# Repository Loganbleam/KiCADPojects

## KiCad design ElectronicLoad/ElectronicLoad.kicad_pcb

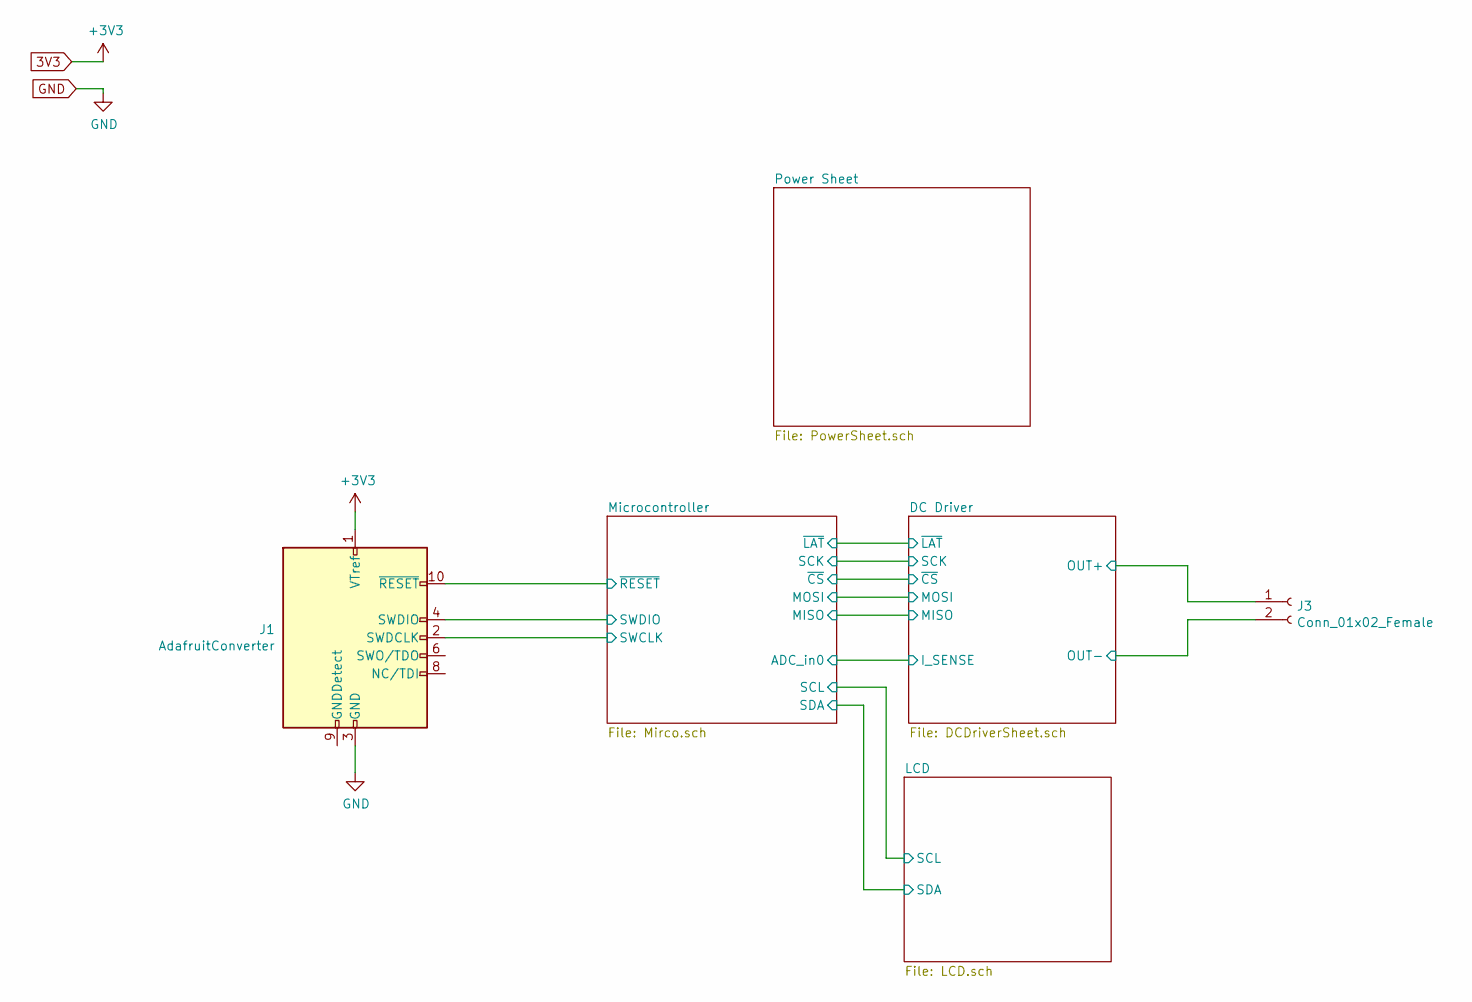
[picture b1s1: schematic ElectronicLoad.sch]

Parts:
J1: AdafruitConverter; PinHeader_2x05_P1.27mm_Vertical_SMD
J3: Conn_01x02_Female; 5.7pitchHoles

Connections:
3V3: J1.1 (VTref); also elsewhere on the board
/Microcontroller/SWCLK: J1.2 (SWDCLK); also elsewhere on the board
/Microcontroller/SWDIO: J1.4 (SWDIO); also elsewhere on the board
/Microcontroller/~RESET: J1.10 (~RESET~); also elsewhere on the board
GND: J1.3 (GND), J1.5 (GND), J1.9 (GNDDetect), J3.2; also elsewhere on the board

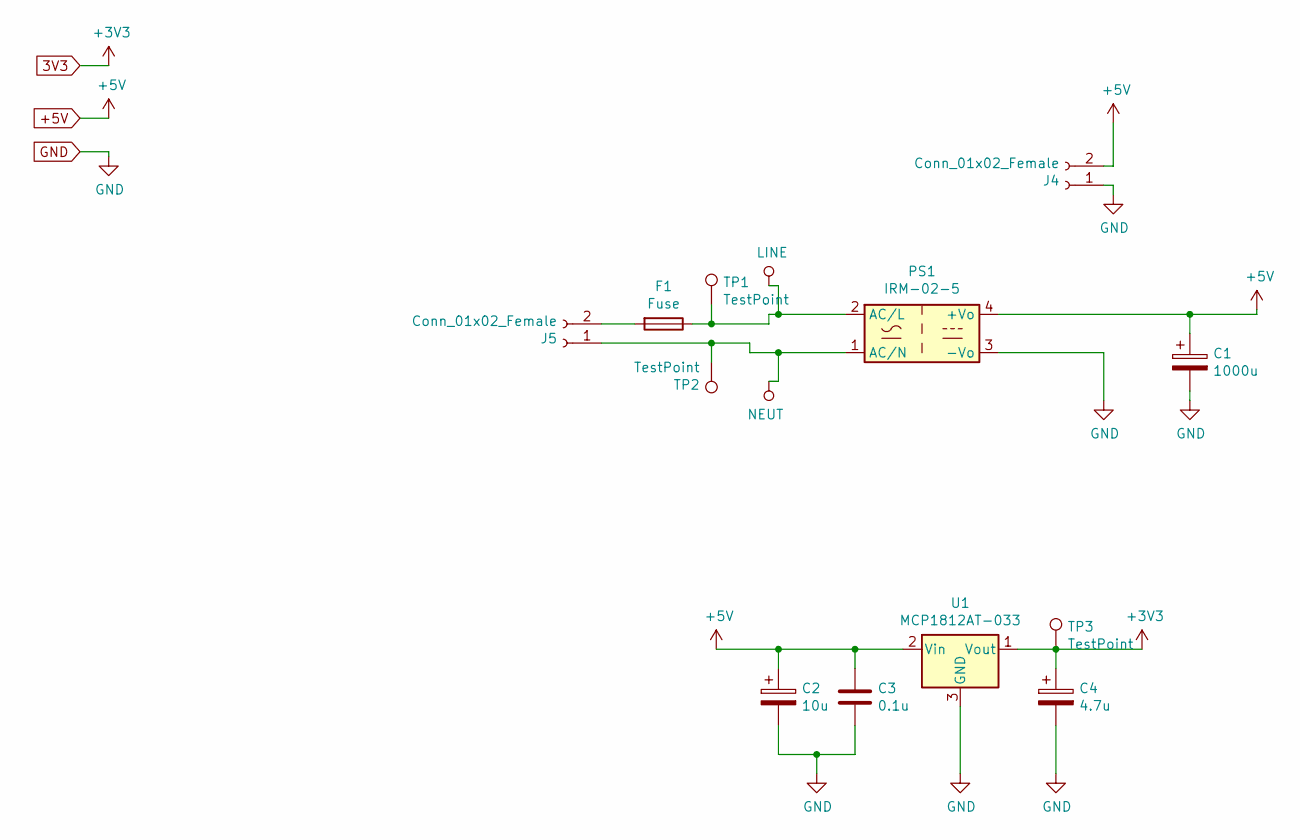
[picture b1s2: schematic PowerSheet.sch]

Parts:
C1: 1000u; CP_Elec_16x17.5
C2: 10u; CP_Elec_6.3x7.7
C3: 0.1u; C_0603_1608Metric
C4: 4.7u; CP_Elec_4x4.5
F1: Fuse; FuseHolder5x20
J4: Conn_01x02_Female; PinSocket_1x02_P2.54mm_Vertical
J5: Conn_01x02_Female; 16GAWire1x02
PS1: IRM-02-5; Converter_ACDC_MeanWell_IRM-02-xx_THT
TP1, TP2, TP3: TestPoint; TestPoint_THTPad_D1.5mm_Drill0.7mm
U1: MCP1812AT-033; SOT-23

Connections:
3V3: C4.1, TP3.1, U1.1 (Vout); also elsewhere on the board
+5V: C1.1, C2.1, C3.1, J4.2, PS1.4 (+Vo), U1.2 (Vin); also elsewhere on the board
GND: C1.2, C2.2, C3.2, C4.2, J4.1, PS1.3 (-Vo), U1.3 (GND); also elsewhere on the board
LINE: F1.1, PS1.2 (AC/L), TP1.1
NEUT: J5.1, PS1.1 (AC/N), TP2.1
unnamed: F1.2, J5.2

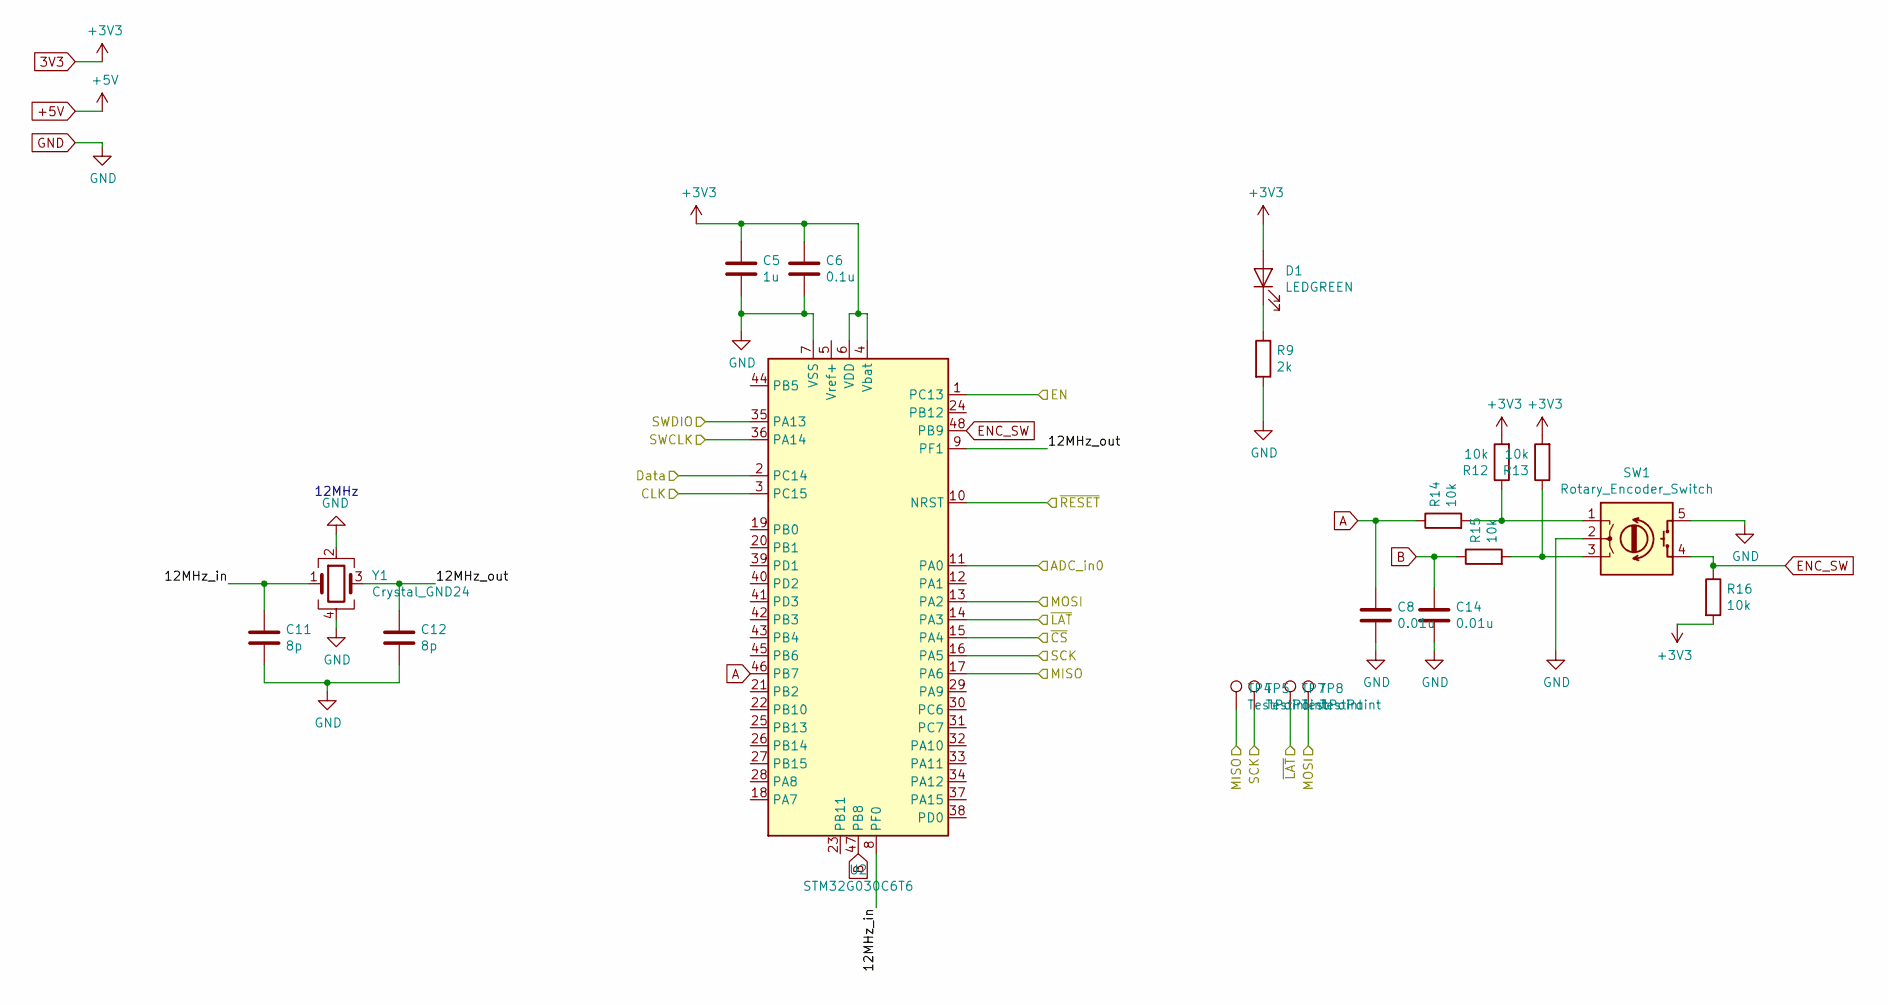
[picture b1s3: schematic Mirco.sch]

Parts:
C5: 1u; C_0603_1608Metric
C6: 0.1u; C_0603_1608Metric
C8, C14: 0.01u; C_0603_1608Metric
C11, C12: 8p; C_0603_1608Metric
D1: LEDGREEN; LED_0603_1608Metric
R9: 2k; R_0603_1608Metric
R12, R13, R14, R15, R16: 10k; R_0603_1608Metric
SW1: Rotary_Encoder_Switch; PinHeader_1x05_P2.54mm_Vertical
TP4, TP5, TP7, TP8: TestPoint; TestPoint_THTPad_D1.5mm_Drill0.7mm
U2: STM32G030C6T6; LQFP-48_7x7mm_P0.5mm
Y1: Crystal_GND24; Crystal_SMD_3225-4Pin_3.2x2.5mm

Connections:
3V3: C5.1, C6.1, D1.2 (A), R12.2, R13.2, R16.2, U2.4 (Vbat), U2.6 (VDD); also elsewhere on the board
/DC Driver/MISO: TP4.1, U2.17 (PA6); also elsewhere on the board
/DC Driver/MOSI: TP8.1, U2.13 (PA2); also elsewhere on the board
/DC Driver/SCK: TP5.1, U2.16 (PA5); also elsewhere on the board
/DC Driver/~CS: U2.15 (PA4); also elsewhere on the board
/DC Driver/~LAT: TP7.1, U2.14 (PA3); also elsewhere on the board
/LCD/CLK: U2.3 (PC15); also elsewhere on the board
/LCD/Data: U2.2 (PC14); also elsewhere on the board
/LCD/EN: U2.1 (PC13); also elsewhere on the board
/Microcontroller/12MHz_in: C11.1, U2.8 (PF0), Y1.1
/Microcontroller/12MHz_out: C12.1, U2.9 (PF1), Y1.3
/Microcontroller/ADC_in0: U2.11 (PA0); also elsewhere on the board
/Microcontroller/SWCLK: U2.36 (PA14); also elsewhere on the board
/Microcontroller/SWDIO: U2.35 (PA13); also elsewhere on the board
/Microcontroller/~RESET: U2.10 (NRST); also elsewhere on the board
A: C8.1, R14.1, U2.46 (PB7)
B: C14.1, R15.1, U2.47 (PB8)
ENC_SW: R16.1, SW1.4 (S2), U2.48 (PB9)
GND: C5.2, C6.2, C8.2, C11.2, C12.2, C14.2, R9.2, SW1.2 (C), SW1.5 (S1), U2.7 (VSS), Y1.2, Y1.4; also elsewhere on the board
unnamed: D1.1 (K), R9.1
unnamed: R12.1, R14.2, SW1.1 (A)
unnamed: R13.1, R15.2, SW1.3 (B)

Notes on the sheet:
12MHz

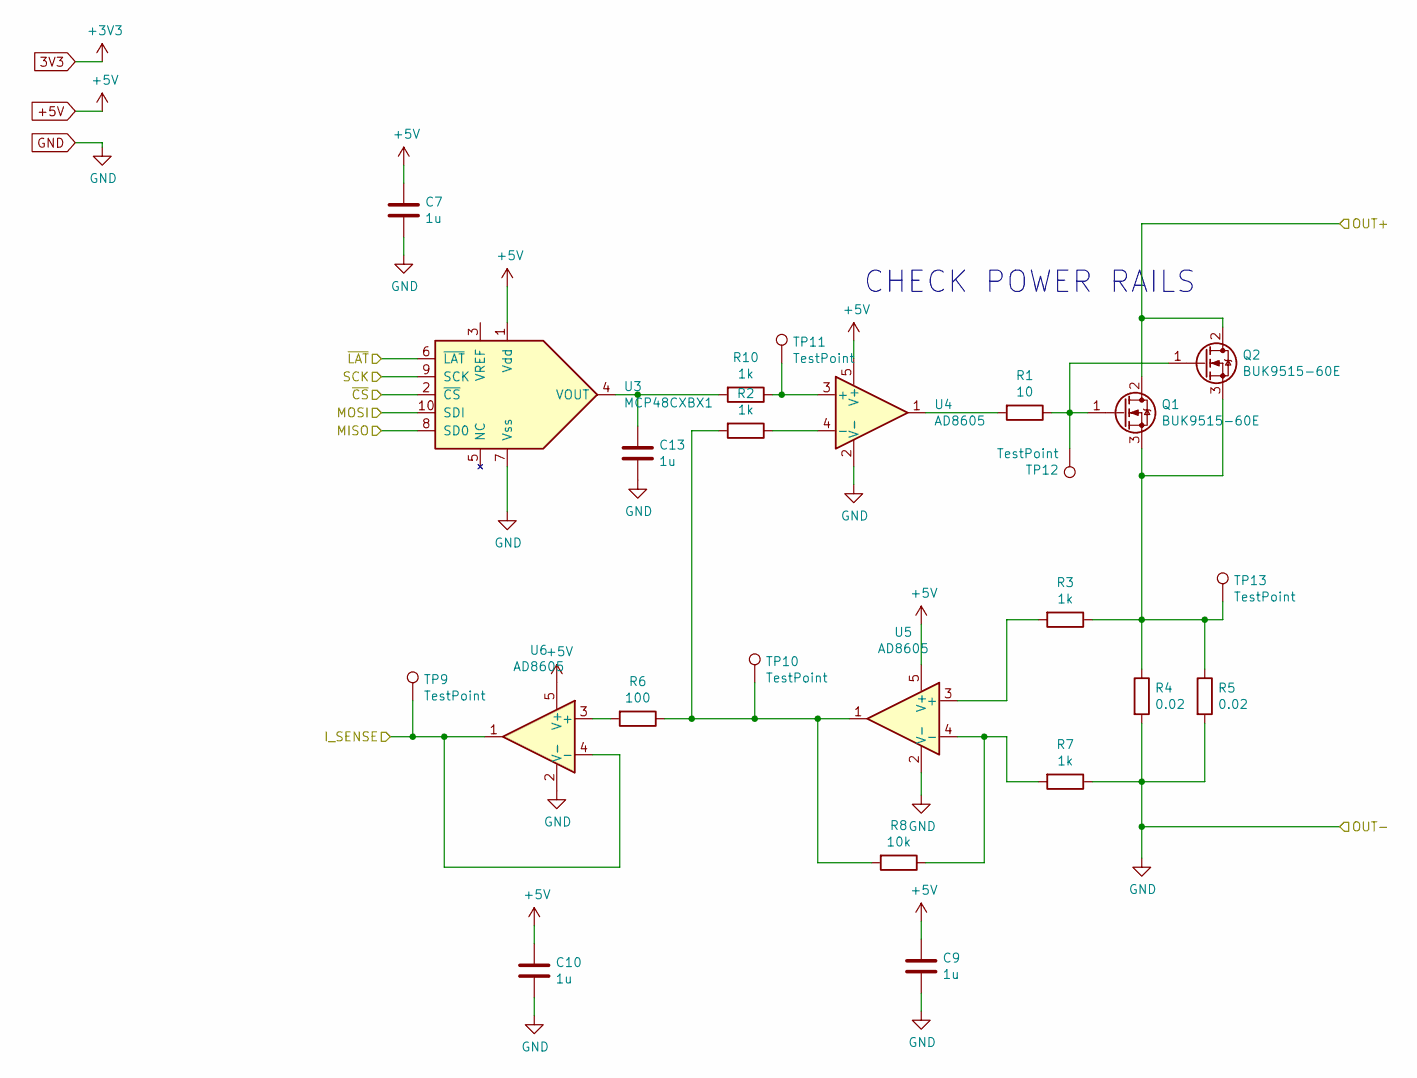
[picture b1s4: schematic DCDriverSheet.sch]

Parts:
C7, C9, C10, C13: 1u; C_0603_1608Metric
Q1, Q2: BUK9515-60E; TO-220-3_Vertical
R1: 10; R_0603_1608Metric
R2, R3, R7, R10: 1k; R_0603_1608Metric
R4, R5: 0.02; R_2512_6332Metric
R6: 100; R_0603_1608Metric
R8: 10k; R_0603_1608Metric
TP9, TP10, TP11, TP12, TP13: TestPoint; TestPoint_THTPad_D1.5mm_Drill0.7mm
U3: MCP48CXBX1; MSOP-10-1EP_3x3mm_P0.5mm_EP1.68x1.88mm
U4, U5, U6: AD8605; TSOT-23-5

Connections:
+5V: C7.1, C9.1, C10.1, U3.1 (Vdd), U4.5 (V+), U5.5 (V+), U6.5 (V+); also elsewhere on the board
/DC Driver/MISO: U3.8 (SD0); also elsewhere on the board
/DC Driver/MOSI: U3.10 (SDI); also elsewhere on the board
/DC Driver/SCK: U3.9 (SCK); also elsewhere on the board
/DC Driver/~CS: U3.2 (~CS); also elsewhere on the board
/DC Driver/~LAT: U3.6 (~LAT); also elsewhere on the board
/Microcontroller/ADC_in0: TP9.1, U6.1, U6.4 (-); also elsewhere on the board
GND: C7.2, C9.2, C10.2, C13.2, R4.2, R5.2, R7.1, U3.7 (Vss), U4.2 (V-), U5.2 (V-), U6.2 (V-); also elsewhere on the board
unnamed: C13.1, R10.2, U3.4 (VOUT)
unnamed: Q1.1 (G), Q2.1 (G), R1.1, TP12.1
unnamed: R1.2, U4.1
unnamed: R2.1, U4.4 (-)
unnamed: R2.2, R6.1, R8.2, TP10.1, U5.1
unnamed: R3.2, U5.3 (+)
unnamed: R6.2, U6.3 (+)
unnamed: R7.2, R8.1, U5.4 (-)
unnamed: R10.1, TP11.1, U4.3 (+)

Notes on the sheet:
CHECK POWER RAILS

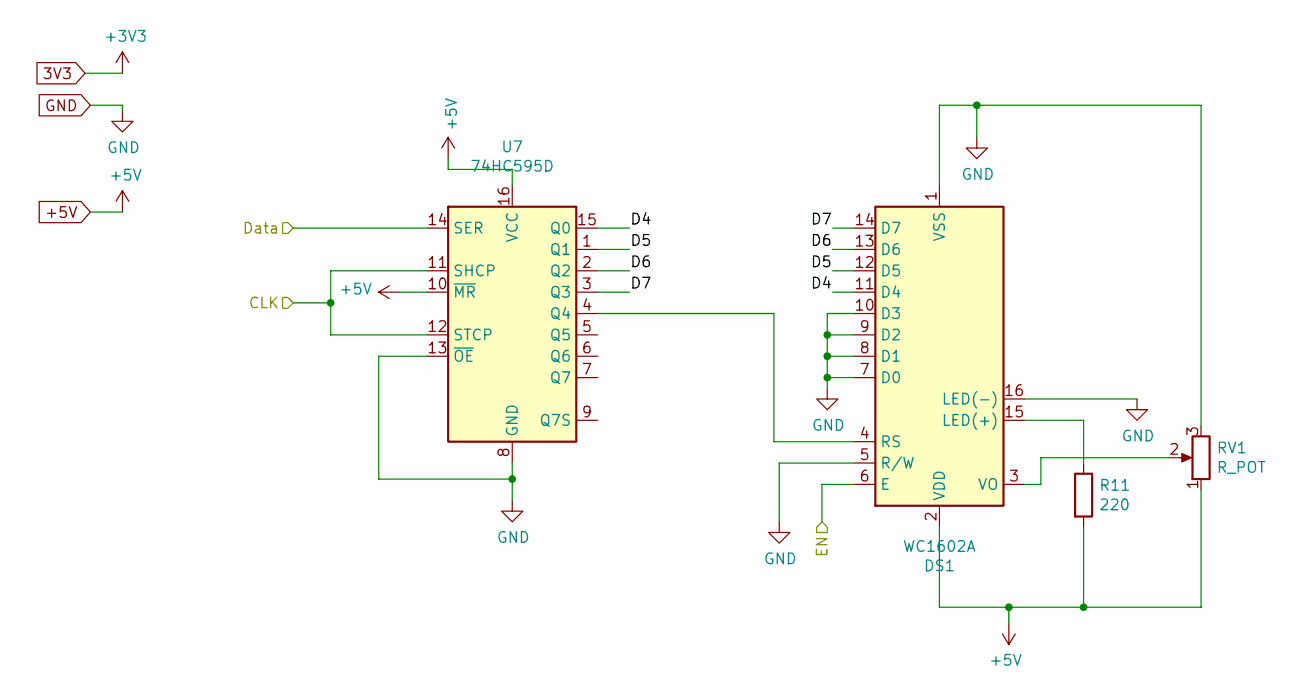
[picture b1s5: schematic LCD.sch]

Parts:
DS1: WC1602A; PinHeader_1x16_P2.54mm_Vertical
R11: 220; R_0603_1608Metric
RV1: R_POT; Potentiometer_Bourns_TC33X-2
U7: 74HC595D; SOIC-16_3.9x9.9mm_P1.27mm

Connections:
+5V: DS1.2 (VDD), R11.2, RV1.1, U7.10 (~MR), U7.16 (VCC); also elsewhere on the board
/LCD/CLK: U7.11 (SHCP), U7.12 (STCP); also elsewhere on the board
/LCD/D4: DS1.11 (D4), U7.15 (Q0)
/LCD/D5: DS1.12 (D5), U7.1 (Q1)
/LCD/D6: DS1.13 (D6), U7.2 (Q2)
/LCD/D7: DS1.14 (D7), U7.3 (Q3)
/LCD/Data: U7.14 (SER); also elsewhere on the board
/LCD/EN: DS1.6 (E); also elsewhere on the board
GND: DS1.1 (VSS), DS1.5 (R/W), DS1.7 (D0), DS1.8 (D1), DS1.9 (D2), DS1.10 (D3), DS1.16 (LED(-)), RV1.3, U7.8 (GND), U7.13 (~OE); also elsewhere on the board
unnamed: DS1.3 (VO), RV1.2
unnamed: DS1.4 (RS), U7.4 (Q4)
unnamed: DS1.15 (LED(+)), R11.1

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
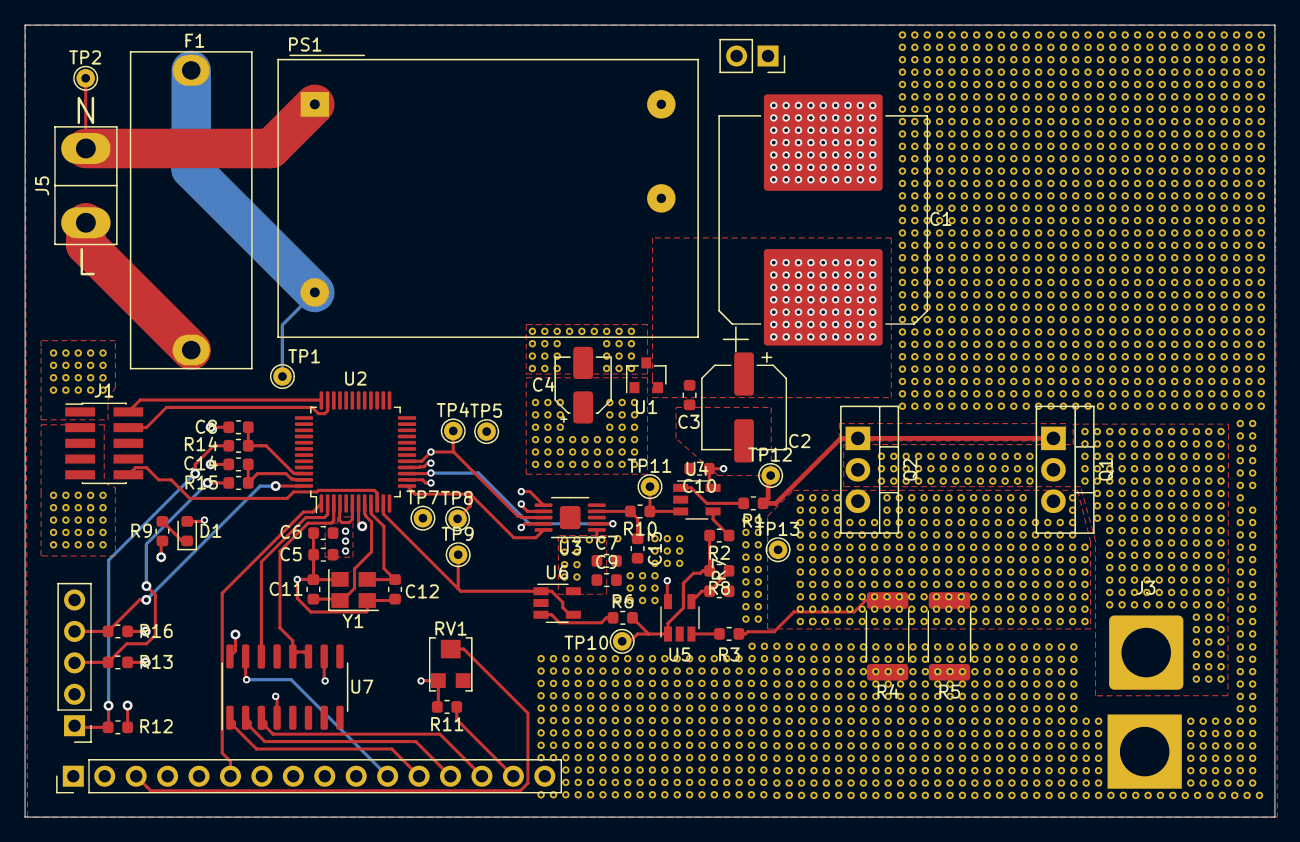
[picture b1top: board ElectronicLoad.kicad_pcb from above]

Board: 4 copper layers, 101.0 x 64.0 mm, 61 parts (0 on the bottom side), 44 nets.

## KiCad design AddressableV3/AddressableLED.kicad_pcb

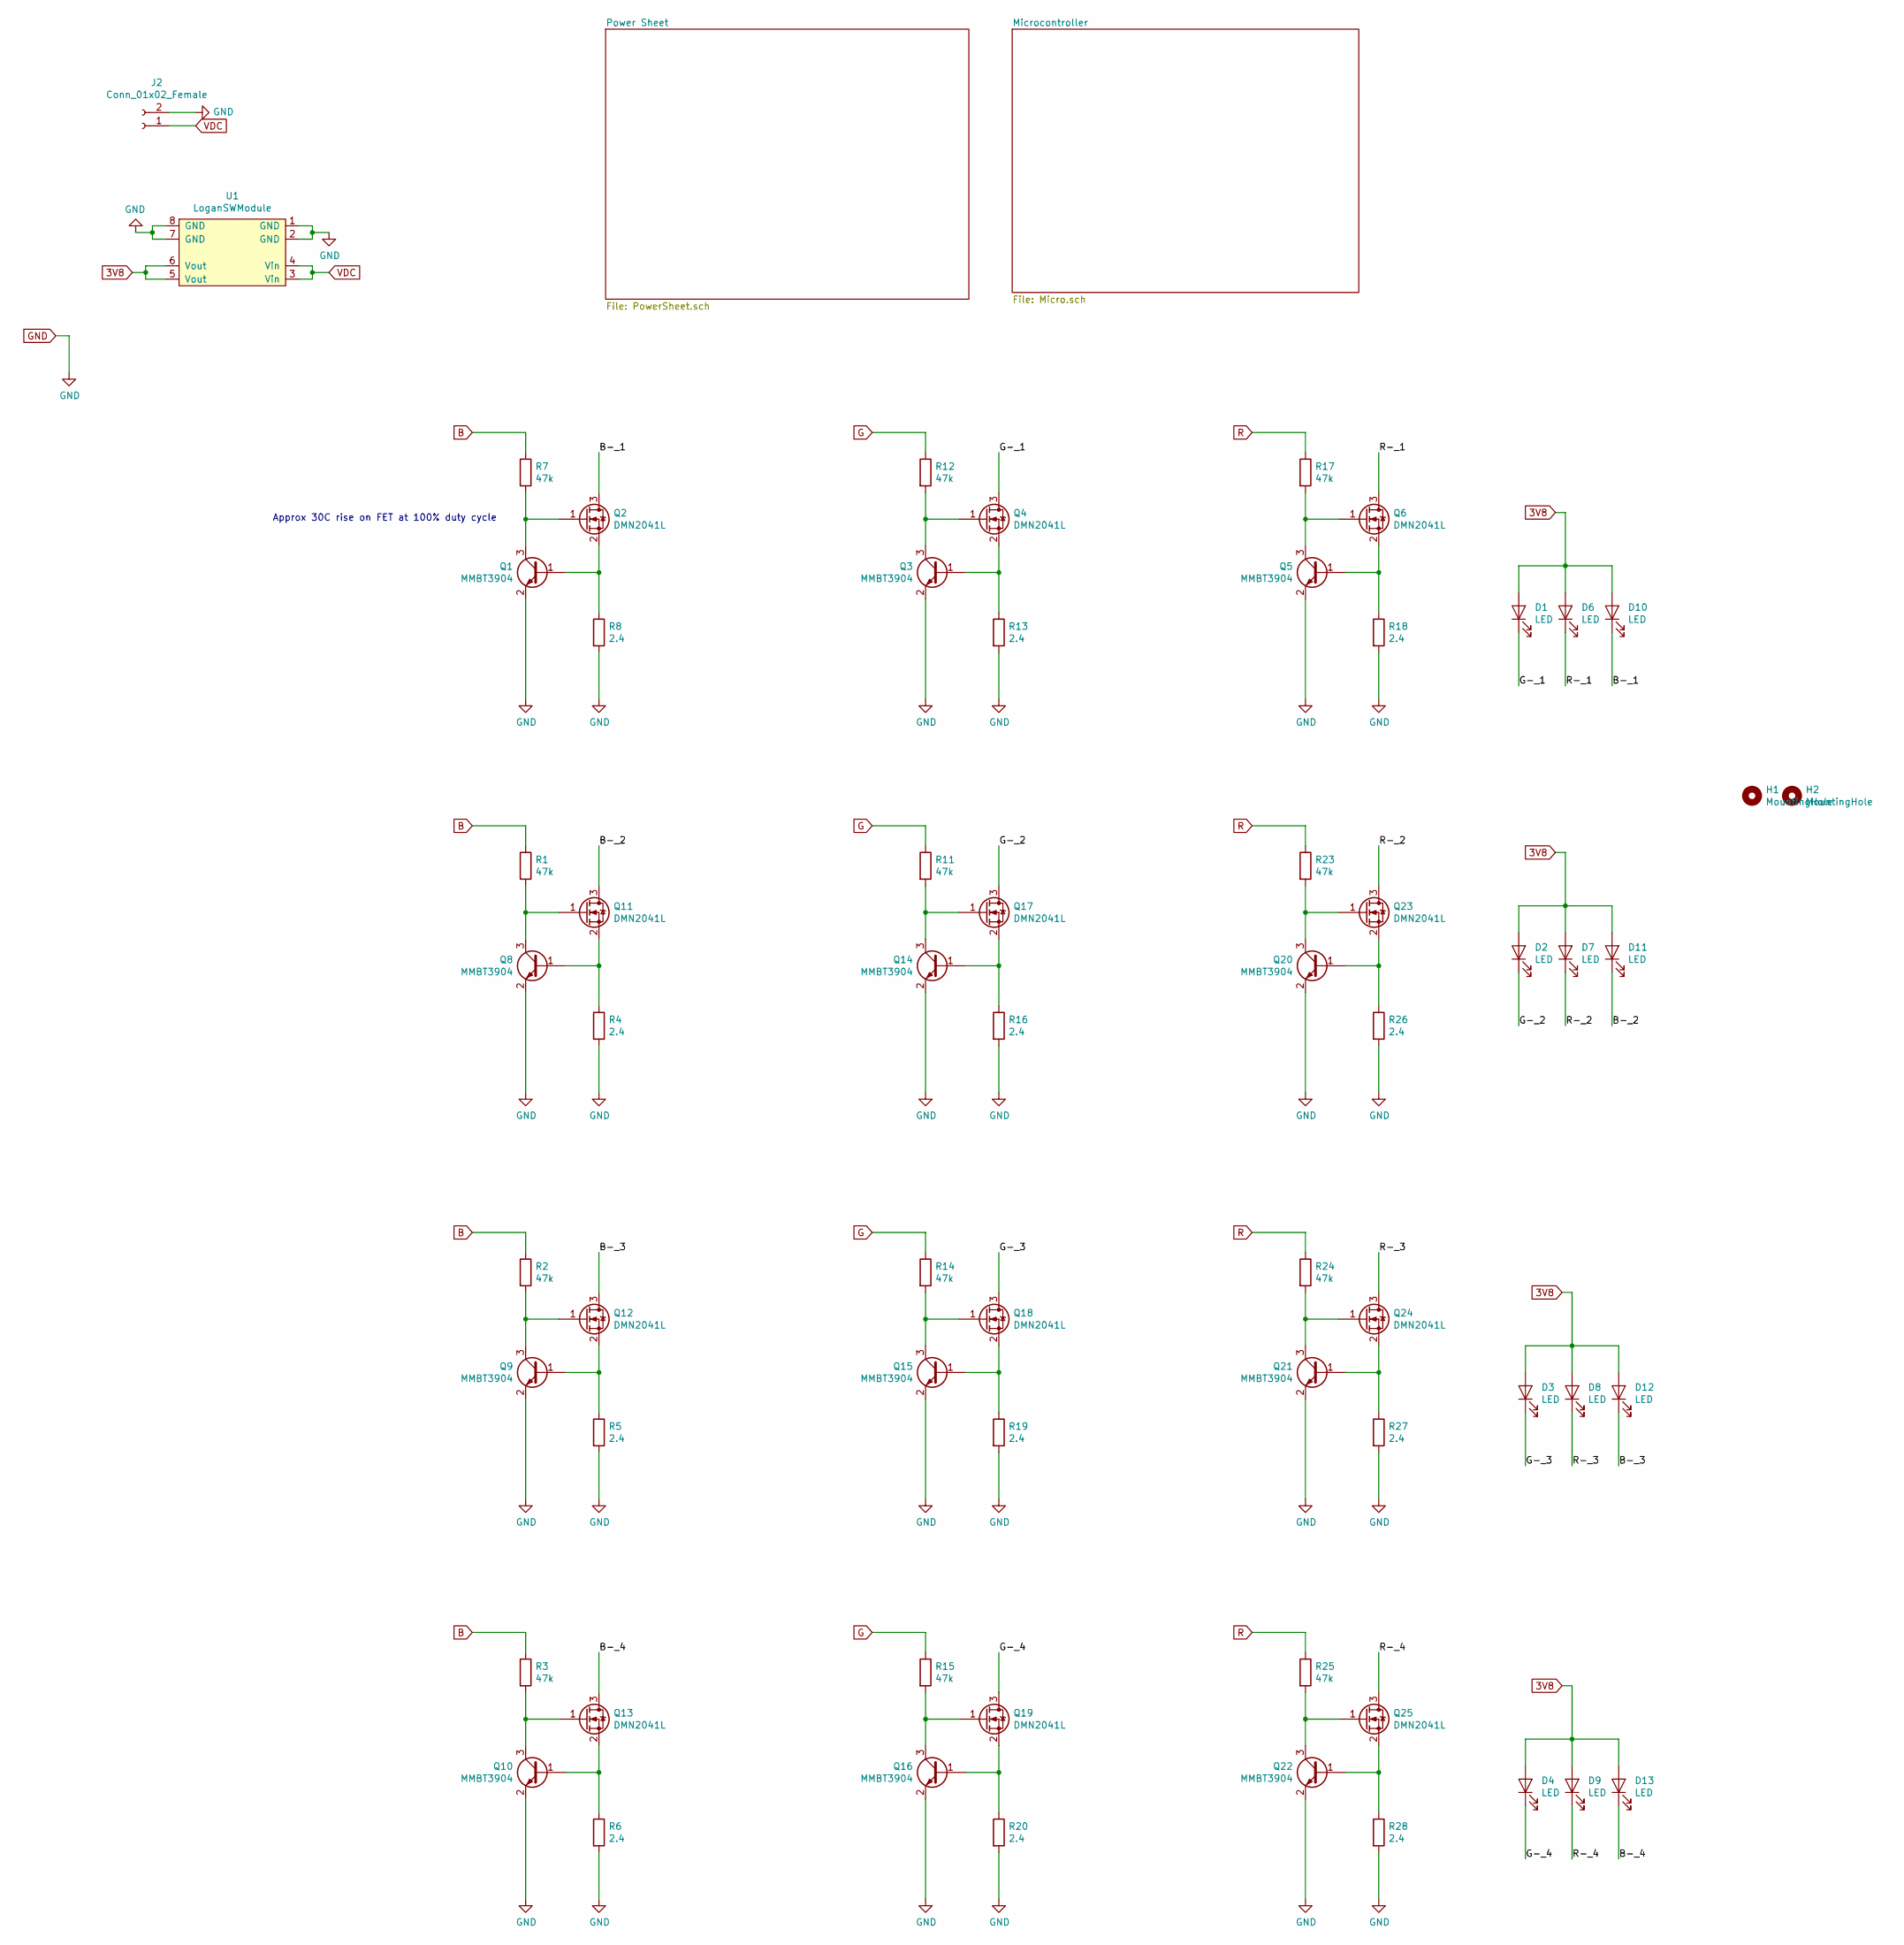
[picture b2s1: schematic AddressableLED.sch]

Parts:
D1, D2, D3, D4, D6, D7, D8, D9, D10, D11, D12, D13: LED; LED_Cree-XQ
H1, H2: MountingHole; MountingHole_3.2mm_M3
J2: Conn_01x02_Female; 1.5mmHole
Q1, Q3, Q5, Q8, Q9, Q10, Q14, Q15, Q16, Q20, Q21, Q22: MMBT3904; SOT-23
Q2, Q4, Q6, Q11, Q12, Q13, Q17, Q18, Q19, Q23, Q24, Q25: DMN2041L; SOT-23
R1, R2, R3, R7, R11, R12, R14, R15, R17, R23, R24, R25: 47k; R_0603_1608Metric
R4, R5, R6, R8, R13, R16, R18, R19, R20, R26, R27, R28: 2.4; R_0805_2012Metric
U1: LoganSWModule; Logan_SWmodule

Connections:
/B-_1: D10.1 (K), Q2.3 (D)
/B-_2: D11.1 (K), Q11.3 (D)
/B-_3: D12.1 (K), Q12.3 (D)
/B-_4: D13.1 (K), Q13.3 (D)
/G-_1: D1.1 (K), Q4.3 (D)
/G-_2: D2.1 (K), Q17.3 (D)
/G-_3: D3.1 (K), Q18.3 (D)
/G-_4: D4.1 (K), Q19.3 (D)
/R-_1: D6.1 (K), Q6.3 (D)
/R-_2: D7.1 (K), Q23.3 (D)
/R-_3: D8.1 (K), Q24.3 (D)
/R-_4: D9.1 (K), Q25.3 (D)
B: R1.1, R2.1, R3.1, R7.1; also elsewhere on the board
G: R11.1, R12.1, R14.1, R15.1; also elsewhere on the board
unnamed: Q1.1 (B), Q2.2 (S), R8.1
unnamed: Q1.3 (C), Q2.1 (G), R7.2
unnamed: Q3.1 (B), Q4.2 (S), R13.1
unnamed: Q3.3 (C), Q4.1 (G), R12.2
unnamed: Q5.1 (B), Q6.2 (S), R18.1
unnamed: Q5.3 (C), Q6.1 (G), R17.2
unnamed: Q10.1 (B), Q13.2 (S), R6.1
unnamed: Q10.3 (C), Q13.1 (G), R3.2
unnamed: Q8.3 (C), Q11.1 (G), R1.2
unnamed: Q8.1 (B), Q11.2 (S), R4.1
unnamed: Q9.3 (C), Q12.1 (G), R2.2
unnamed: Q9.1 (B), Q12.2 (S), R5.1
unnamed: Q14.1 (B), Q17.2 (S), R16.1
unnamed: Q14.3 (C), Q17.1 (G), R11.2
unnamed: Q15.1 (B), Q18.2 (S), R19.1
unnamed: Q15.3 (C), Q18.1 (G), R14.2
unnamed: Q16.1 (B), Q19.2 (S), R20.1
unnamed: Q16.3 (C), Q19.1 (G), R15.2
unnamed: Q20.1 (B), Q23.2 (S), R26.1
unnamed: Q20.3 (C), Q23.1 (G), R23.2
unnamed: Q21.1 (B), Q24.2 (S), R27.1
unnamed: Q21.3 (C), Q24.1 (G), R24.2
unnamed: Q22.1 (B), Q25.2 (S), R28.1
unnamed: Q22.3 (C), Q25.1 (G), R25.2
R: R17.1, R23.1, R24.1, R25.1; also elsewhere on the board
VDC: J2.1, U1.3 (Vin), U1.4 (Vin)

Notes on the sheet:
Approx 30C rise on FET at 100% duty cycle

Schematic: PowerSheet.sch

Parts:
C1: 0.1u; C_0603_1608Metric
C2, C3, C6, C7, C8, C9: 22u; C_0603_1608Metric
D5: LED; LED_0603_1608Metric
L1: 2.2u; L_Coilcraft_XxL4020
R10: 10k; R_0603_1608Metric
R21: 36k; R_0603_1608Metric
R22: 1k; R_0603_1608Metric
U1: TPS563200; SOT-23-6
U2: MCP1812AT-033_TT; SOT-23

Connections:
unnamed: C6.1, C7.1
unnamed: D5.1 (K), R22.1

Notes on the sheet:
Output = 2.7V with 1k Res

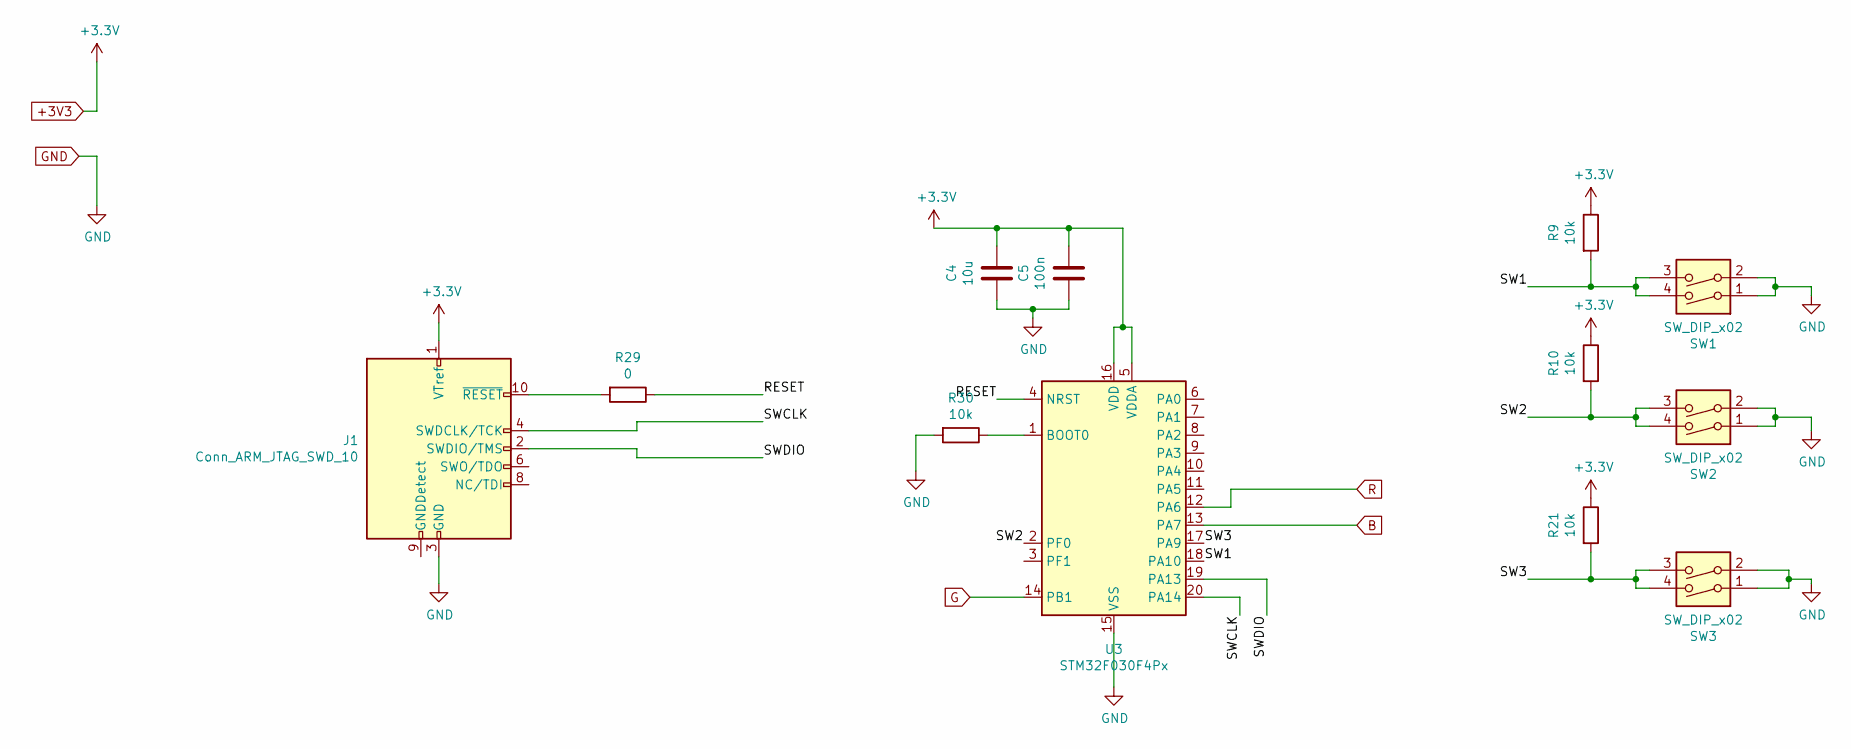
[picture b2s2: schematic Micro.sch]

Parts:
C4: 10u; C_0603_1608Metric
C5: 100n; C_0603_1608Metric
J1: Conn_ARM_JTAG_SWD_10; PinHeader_2x05_P1.27mm_Vertical_SMD
R9, R10, R21, R30: 10k; R_0603_1608Metric
R29: 0; R_0603_1608Metric
SW1, SW2, SW3: SW_DIP_x02; SideMountSwitch
U3: STM32F030F4Px; TSSOP-20_4.4x6.5mm_P0.65mm

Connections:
/Microcontroller/RESET: R29.1, U3.4 (NRST)
/Microcontroller/SW1: R9.2, SW1.3, SW1.4, U3.18 (PA10)
/Microcontroller/SWCLK: J1.4 (SWDCLK/TCK), U3.20 (PA14)
/Microcontroller/SWDIO: J1.2 (SWDIO/TMS), U3.19 (PA13)
B: U3.13 (PA7); also elsewhere on the board
G: U3.14 (PB1); also elsewhere on the board
unnamed: J1.10 (~RESET~), R29.2
unnamed: R30.1, U3.1 (BOOT0)
R: U3.12 (PA6); also elsewhere on the board

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
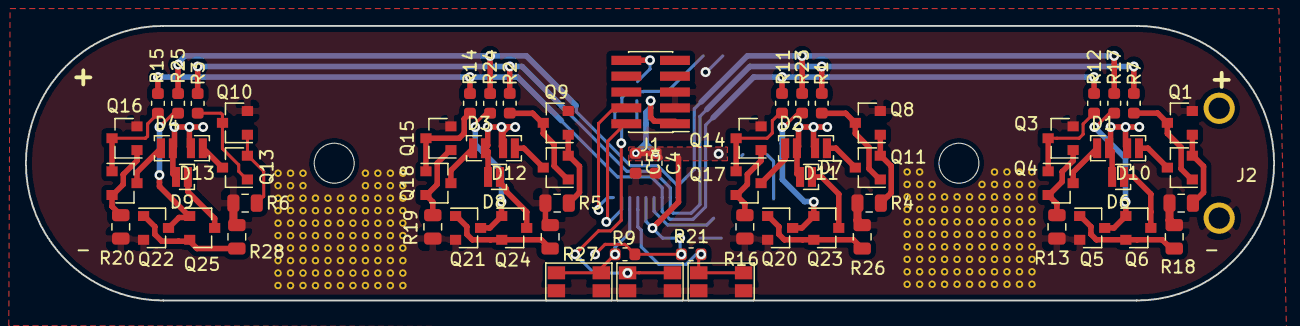
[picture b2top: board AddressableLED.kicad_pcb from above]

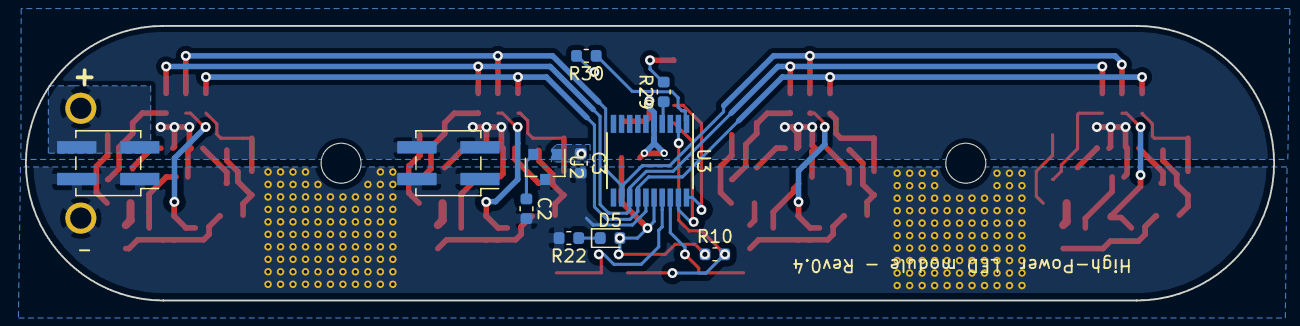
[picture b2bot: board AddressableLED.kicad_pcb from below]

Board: 2 copper layers, 100.0 x 22.0 mm, 81 parts (10 on the bottom side), 52 nets.

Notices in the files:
parts and their libraries:
Copyright 2016 Accelerated Designs. All rights reserved.
